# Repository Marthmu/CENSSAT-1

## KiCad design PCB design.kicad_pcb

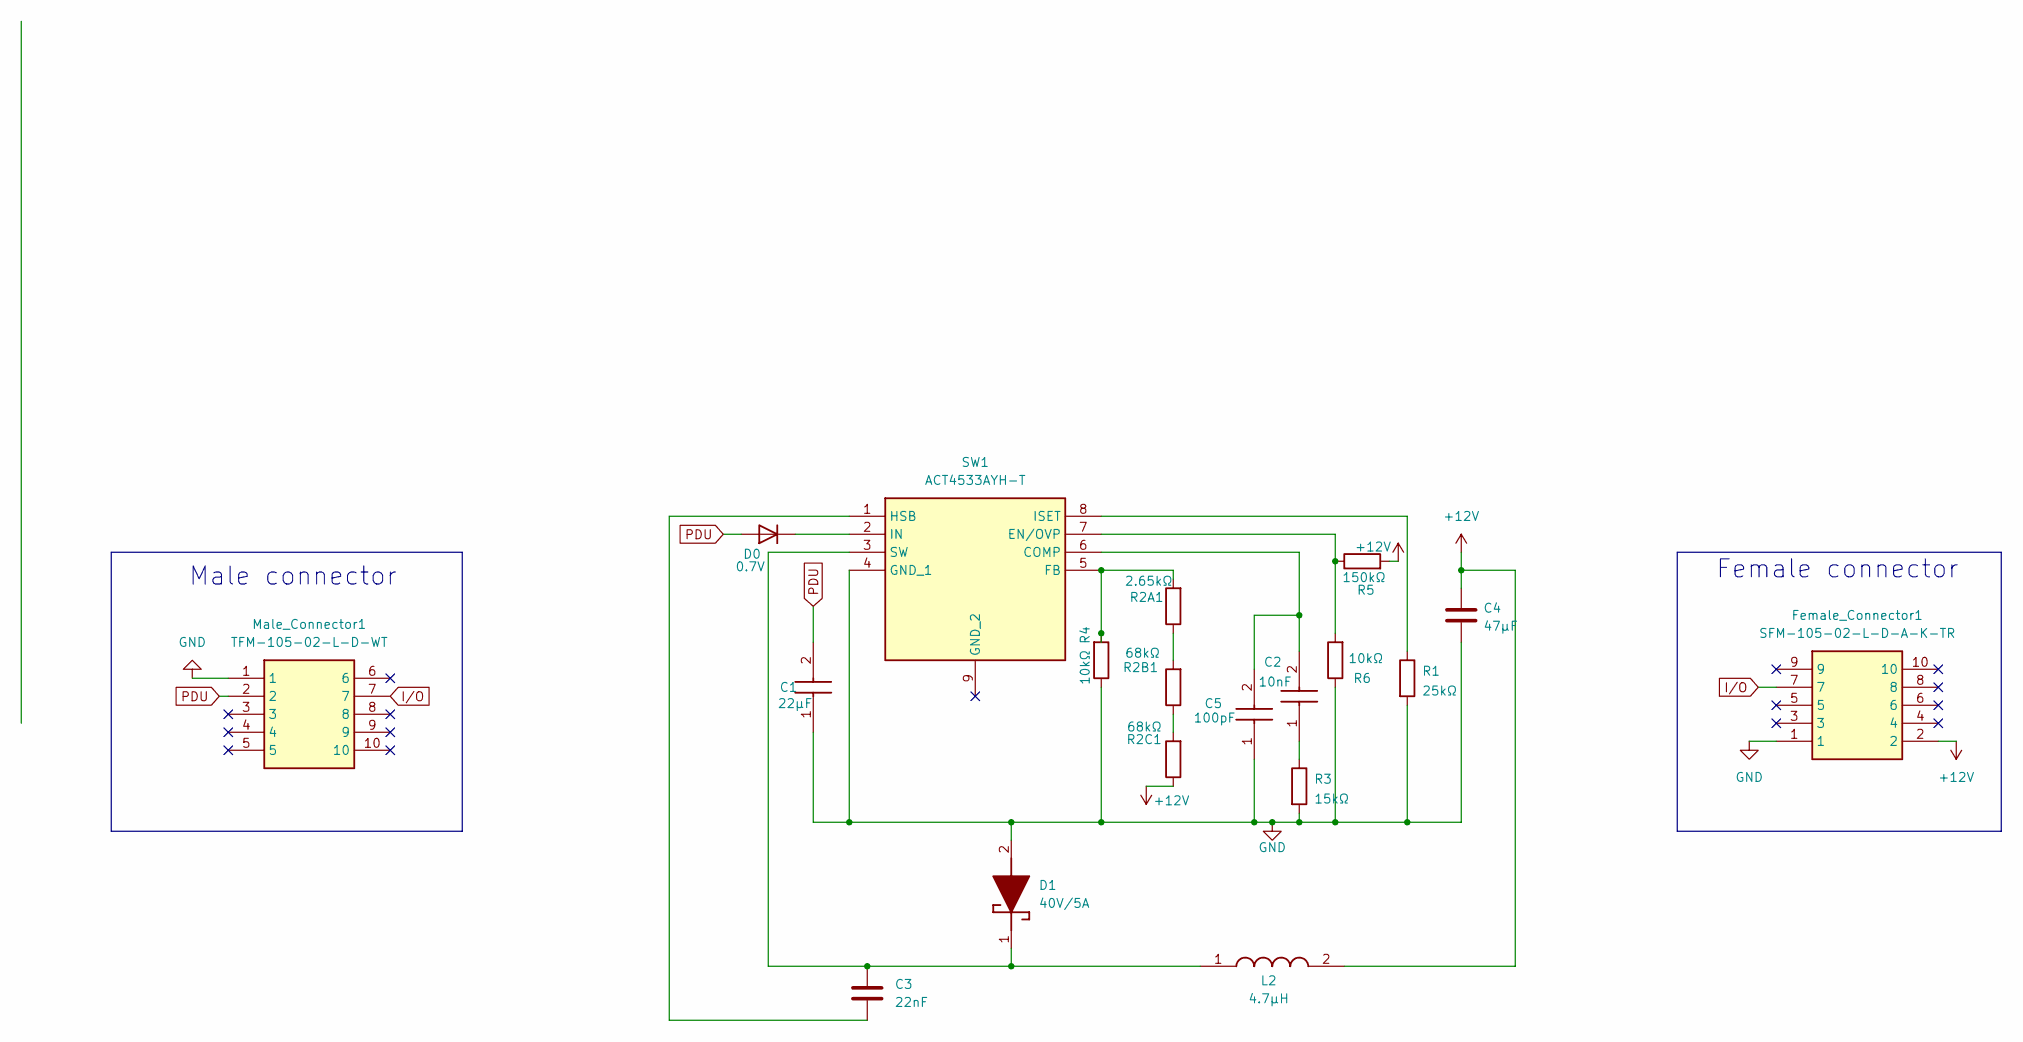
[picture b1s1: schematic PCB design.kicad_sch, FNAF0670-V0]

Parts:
C1: 22µF; C_1812_4532Metric_Pad1.57x3.40mm_HandSolder; Mouser Part Number 75-MKP1839110631
C2: 10nF; C_1206_3216Metric_Pad1.33x1.80mm_HandSolder; Mouser Part Number 594-D103K69Y5PL63L0R
C3: 22nF; C_1206_3216Metric_Pad1.33x1.80mm_HandSolder
C4: 47µF; C_1808_4520Metric_Pad1.72x2.30mm_HandSolder
C5: 100pF; C_1808_4520Metric_Pad1.72x2.30mm_HandSolder; Mouser Part Number 75-MKT1813322405G
D0: 0.7V; D_2010_5025Metric_Pad1.52x2.65mm_HandSolder
D1: 40V/5A; D_2010_5025Metric_Pad1.52x2.65mm_HandSolder; Mouser Part Number 241-SK54BLF_R1_00001
Female_Connector1: SFM-105-02-L-D-A-K-TR; SFM-105-YY-XXX-D-A-K-TR; Mouser Part Number 200-SFM10502LDAKTR
L2: 4.7µH; L_10.4x10.4_H4.8; Mouser Part Number 963-LB3218T102K
Male_Connector1: TFM-105-02-L-D-WT; TFM-105-02-XXX-D-WT; Mouser Part Number 200-TFM10502LDWT
R1: 25kΩ; R_1206_3216Metric_Pad1.30x1.75mm_HandSolder
R2A1: 2.65kΩ; R_1206_3216Metric_Pad1.30x1.75mm_HandSolder
R2B1, R2C1: 68kΩ; R_1206_3216Metric_Pad1.30x1.75mm_HandSolder
R3: 15kΩ; R_1206_3216Metric_Pad1.30x1.75mm_HandSolder
R4, R6: 10kΩ; R_1206_3216Metric_Pad1.30x1.75mm_HandSolder
R5: 150kΩ; R_1206_3216Metric_Pad1.30x1.75mm_HandSolder
SW1: ACT4533AYH-T; SOIC127P600X170-9N; Manufacturer_Part_Number ACT4533AYH-T; Mouser Part Number 107-ACT4533AYH-T

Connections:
+12V: C4.1, Female_Connector1.2, L2.2, R2C1.1, R5.2
GND: C1.1 (+), C4.2, C5.1 (+), D1.2 (A), Female_Connector1.1, Male_Connector1.1, R1.2, R3.2, R4.1, R6.1, SW1.4 (GND_1)
I/O: Female_Connector1.7, Male_Connector1.7
unnamed: C2.1, R3.1
unnamed: C2.2, C5.2 (-), SW1.6 (COMP)
unnamed: D0.1 (K), SW1.2 (IN)
unnamed: C3.1, D1.1 (K), L2.1, SW1.3 (SW)
unnamed: R2A1.1, R2B1.2
unnamed: R2B1.1, R2C1.2
unnamed: R5.1, R6.2, SW1.7 (EN/OVP)
unnamed: R2A1.2, R4.2, SW1.5 (FB)
unnamed: C3.2, SW1.1 (HSB)
unnamed: R1.1, SW1.8 (ISET)
PDU: C1.2 (-), D0.2 (A), Male_Connector1.2

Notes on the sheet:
Female connector
Male connector

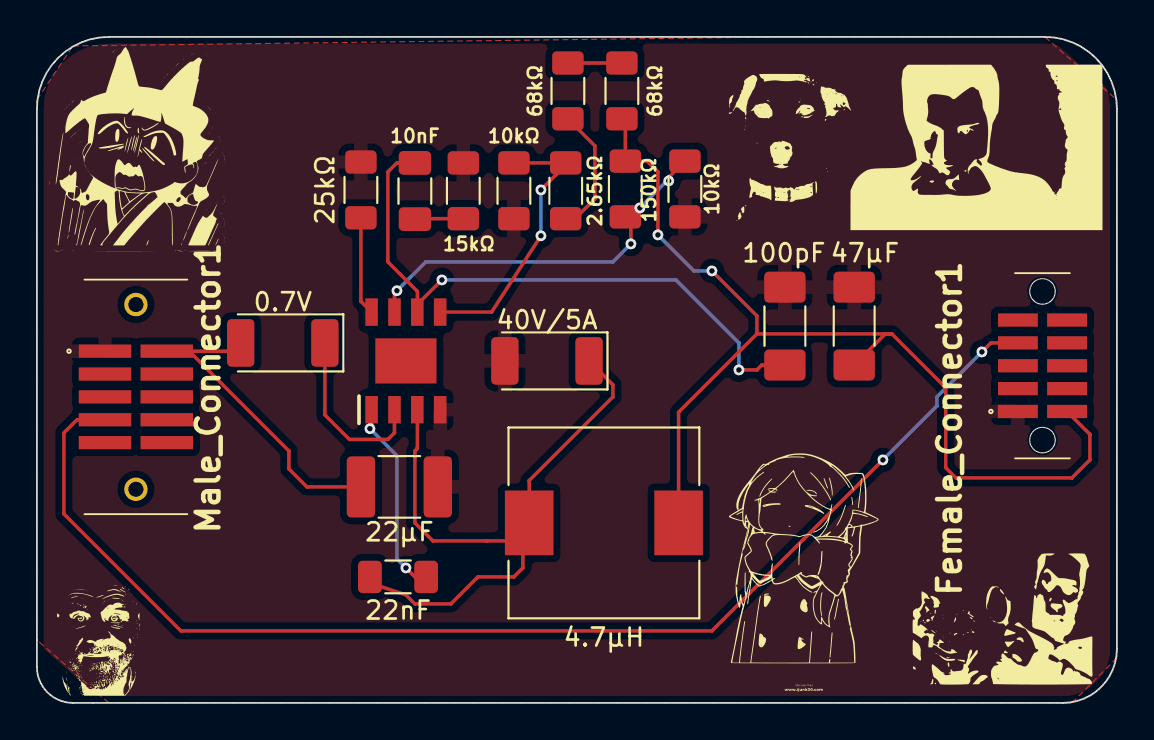
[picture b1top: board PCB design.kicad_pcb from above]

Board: 2 copper layers, 60.0 x 37.0 mm, 19 parts (0 on the bottom side), 14 nets.
